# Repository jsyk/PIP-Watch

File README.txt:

----------------------------------------
Personal Information Panel - PIP Watch
----------------------------------------

Personal Information Panel – PIP Watch – is an open-source smart watch with an ePaper (EPD) display, a Bluetooth connection, and a Li-Ion accumulator.

This is a work in progress... For more information please visit:
http://www.jsykora.info/?page_id=328

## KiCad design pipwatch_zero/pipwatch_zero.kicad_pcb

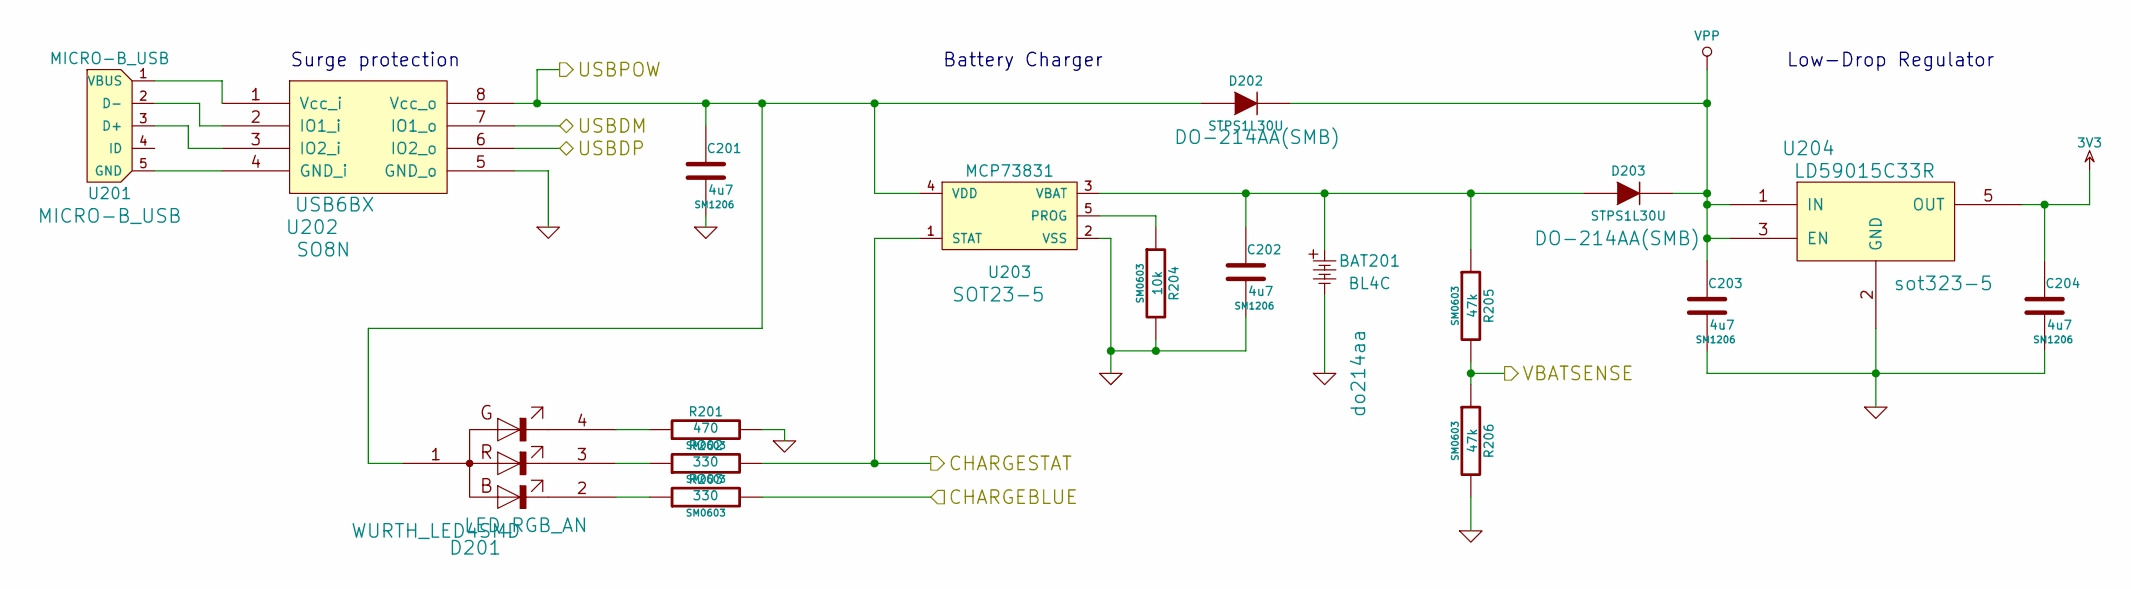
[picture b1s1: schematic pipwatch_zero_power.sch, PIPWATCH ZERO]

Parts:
BAT201: BL4C; do214aa
C201, C202, C203, C204: 4u7; SM1206
D201: LED_RGB_AN; WURTH_LED4SMD
D202, D203: STPS1L30U; DO-214AA(SMB)
R201: 470; SM0603
R202, R203: 330; SM0603
R204: 10k; SM0603
R205, R206: 47k; SM0603
U201: MICRO-B_USB
U202: USB6BX; SO8N
U203: MCP73831; SOT23-5
U204: LD59015C33R; sot323-5

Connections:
3V3: C204.1, U204.5 (OUT); also elsewhere on the board
/Battery and Power/CHARGEBLUE: R203.2; also elsewhere on the board
/Battery and Power/CHARGESTAT: R202.2, U203.1 (STAT); also elsewhere on the board
/Battery and Power/USBDM: U202.7 (IO1_o); also elsewhere on the board
/Battery and Power/USBDP: U202.6 (IO2_o); also elsewhere on the board
/Battery and Power/USBPOW: C201.1, D201.1, D202.1 (A), U202.8 (Vcc_o), U203.4 (VDD); also elsewhere on the board
/Battery and Power/VBATSENSE: R205.2, R206.1; also elsewhere on the board
GND: BAT201.2, C201.2, C202.2, C203.2, C204.2, R201.2, R204.2, R206.2, U202.5 (GND_o), U203.2 (VSS), U204.2 (GND); also elsewhere on the board
unnamed: R204.1, U203.5 (PROG)
unnamed: D201.4, R201.1
unnamed: D201.3, R202.1
unnamed: D201.2, R203.1
unnamed: U201.3 (D+), U202.3 (IO2_i)
unnamed: U201.2 (D-), U202.2 (IO1_i)
unnamed: U201.1 (VBUS), U202.1 (Vcc_i)
unnamed: U201.5 (GND), U202.4 (GND_i)
unnamed: BAT201.1, C202.1, D203.1 (A), R205.1, U203.3 (VBAT)
VPP: C203.1, D202.2 (K), D203.2 (K), U204.1 (IN), U204.3 (EN); also elsewhere on the board

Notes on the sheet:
Surge protection
Battery Charger
Low-Drop Regulator

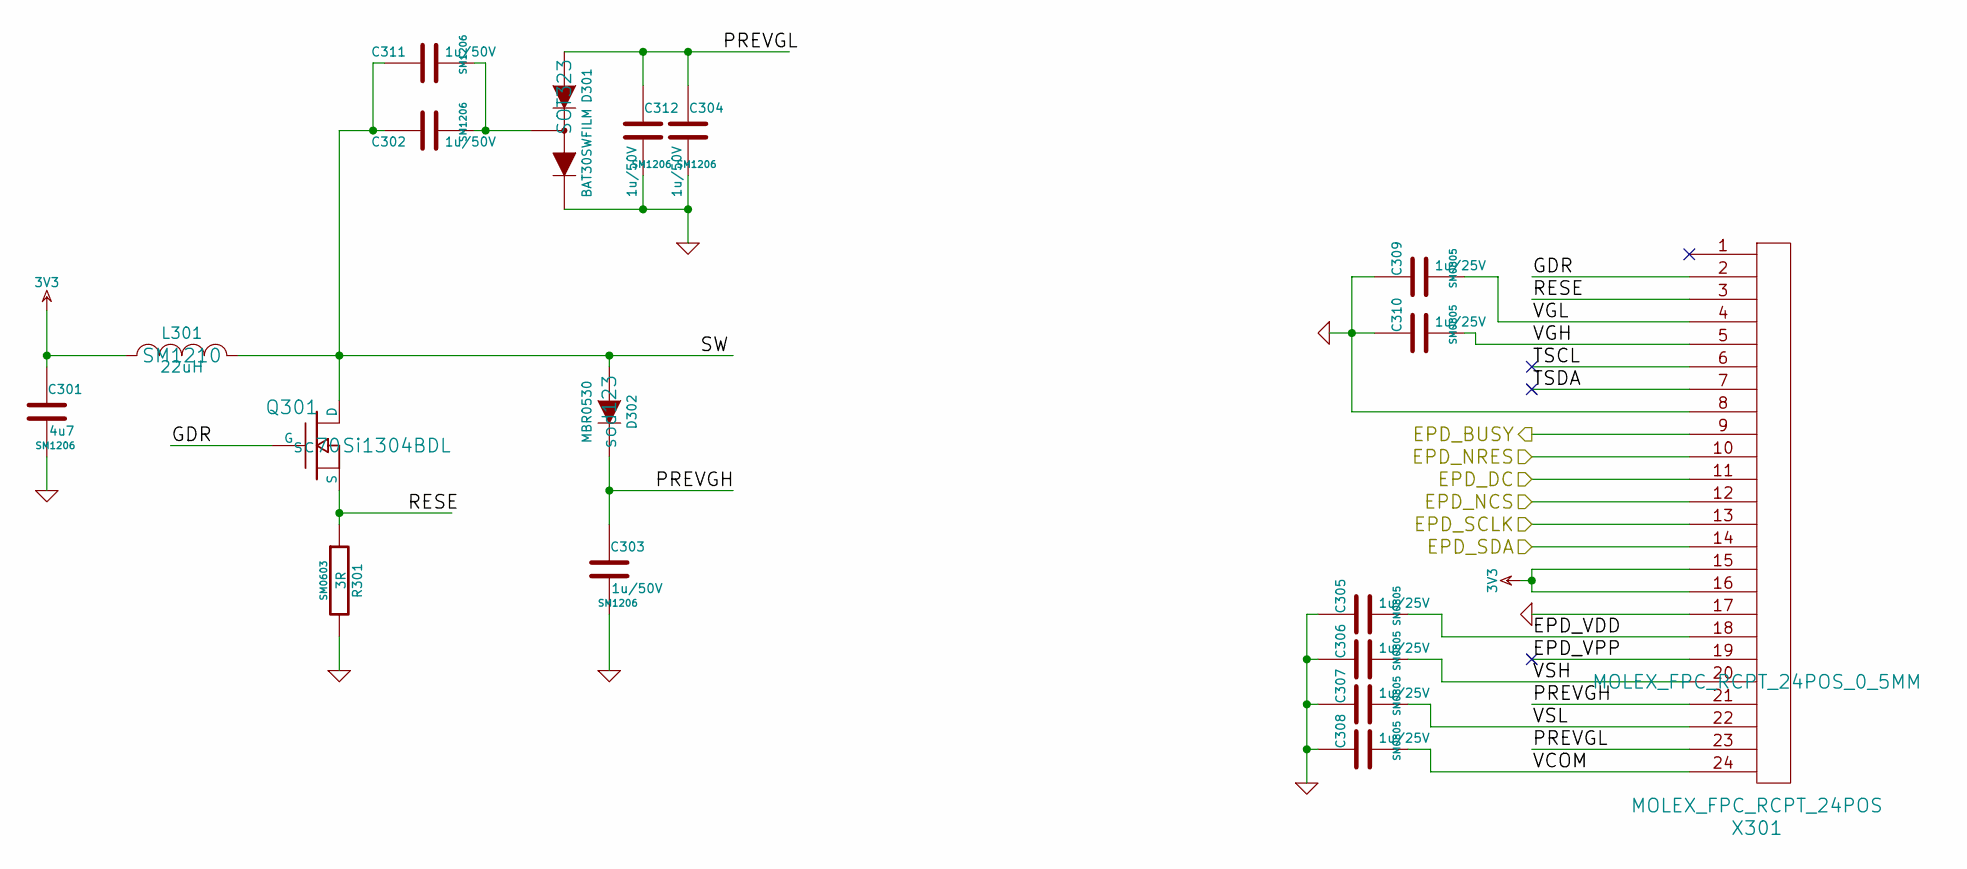
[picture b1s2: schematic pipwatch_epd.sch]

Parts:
C301: 4u7; SM1206
C302, C303, C304, C311, C312: 1u/50V; SM1206
C305, C306, C307, C308, C309, C310: 1u/25V; SM0805
D301: BAT30SWFILM; SOT323
D302: MBR0530; sod123
L301: 22uH; SM1210
Q301: Si1304BDL; sc70
R301: 3R; SM0603
X301: MOLEX_FPC_RCPT_24POS; MOLEX_FPC_RCPT_24POS_0_5MM

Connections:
3V3: C301.1, L301.1, X301.15, X301.16; also elsewhere on the board
/CPU/EPD_BUSY: X301.9; also elsewhere on the board
/CPU/EPD_DC: X301.11; also elsewhere on the board
/CPU/EPD_NCS: X301.12; also elsewhere on the board
/CPU/EPD_NRES: X301.10; also elsewhere on the board
/CPU/EPD_SCLK: X301.13; also elsewhere on the board
/CPU/EPD_SDA: X301.14; also elsewhere on the board
/EP-Display/EPD_VDD: C305.2, X301.18
/EP-Display/GDR: Q301.1 (G), X301.2
/EP-Display/PREVGH: C303.1, D302.2 (K), X301.21
/EP-Display/PREVGL: C304.1, C312.1, D301.1 (A), X301.23
/EP-Display/RESE: Q301.3 (S), R301.1, X301.3
/EP-Display/SW: C302.1, C311.1, D302.1 (A), L301.2, Q301.2 (D)
/EP-Display/VCOM: C308.2, X301.24
/EP-Display/VGH: C310.2, X301.5
/EP-Display/VGL: C309.2, X301.4
/EP-Display/VSH: C306.2, X301.20
/EP-Display/VSL: C307.2, X301.22
GND: C301.2, C303.2, C304.2, C305.1, C306.1, C307.1, C308.1, C309.1, C310.1, C312.2, D301.2 (K), R301.2, X301.8, X301.17; also elsewhere on the board
unnamed: C302.2, C311.2, D301.3 (Com)

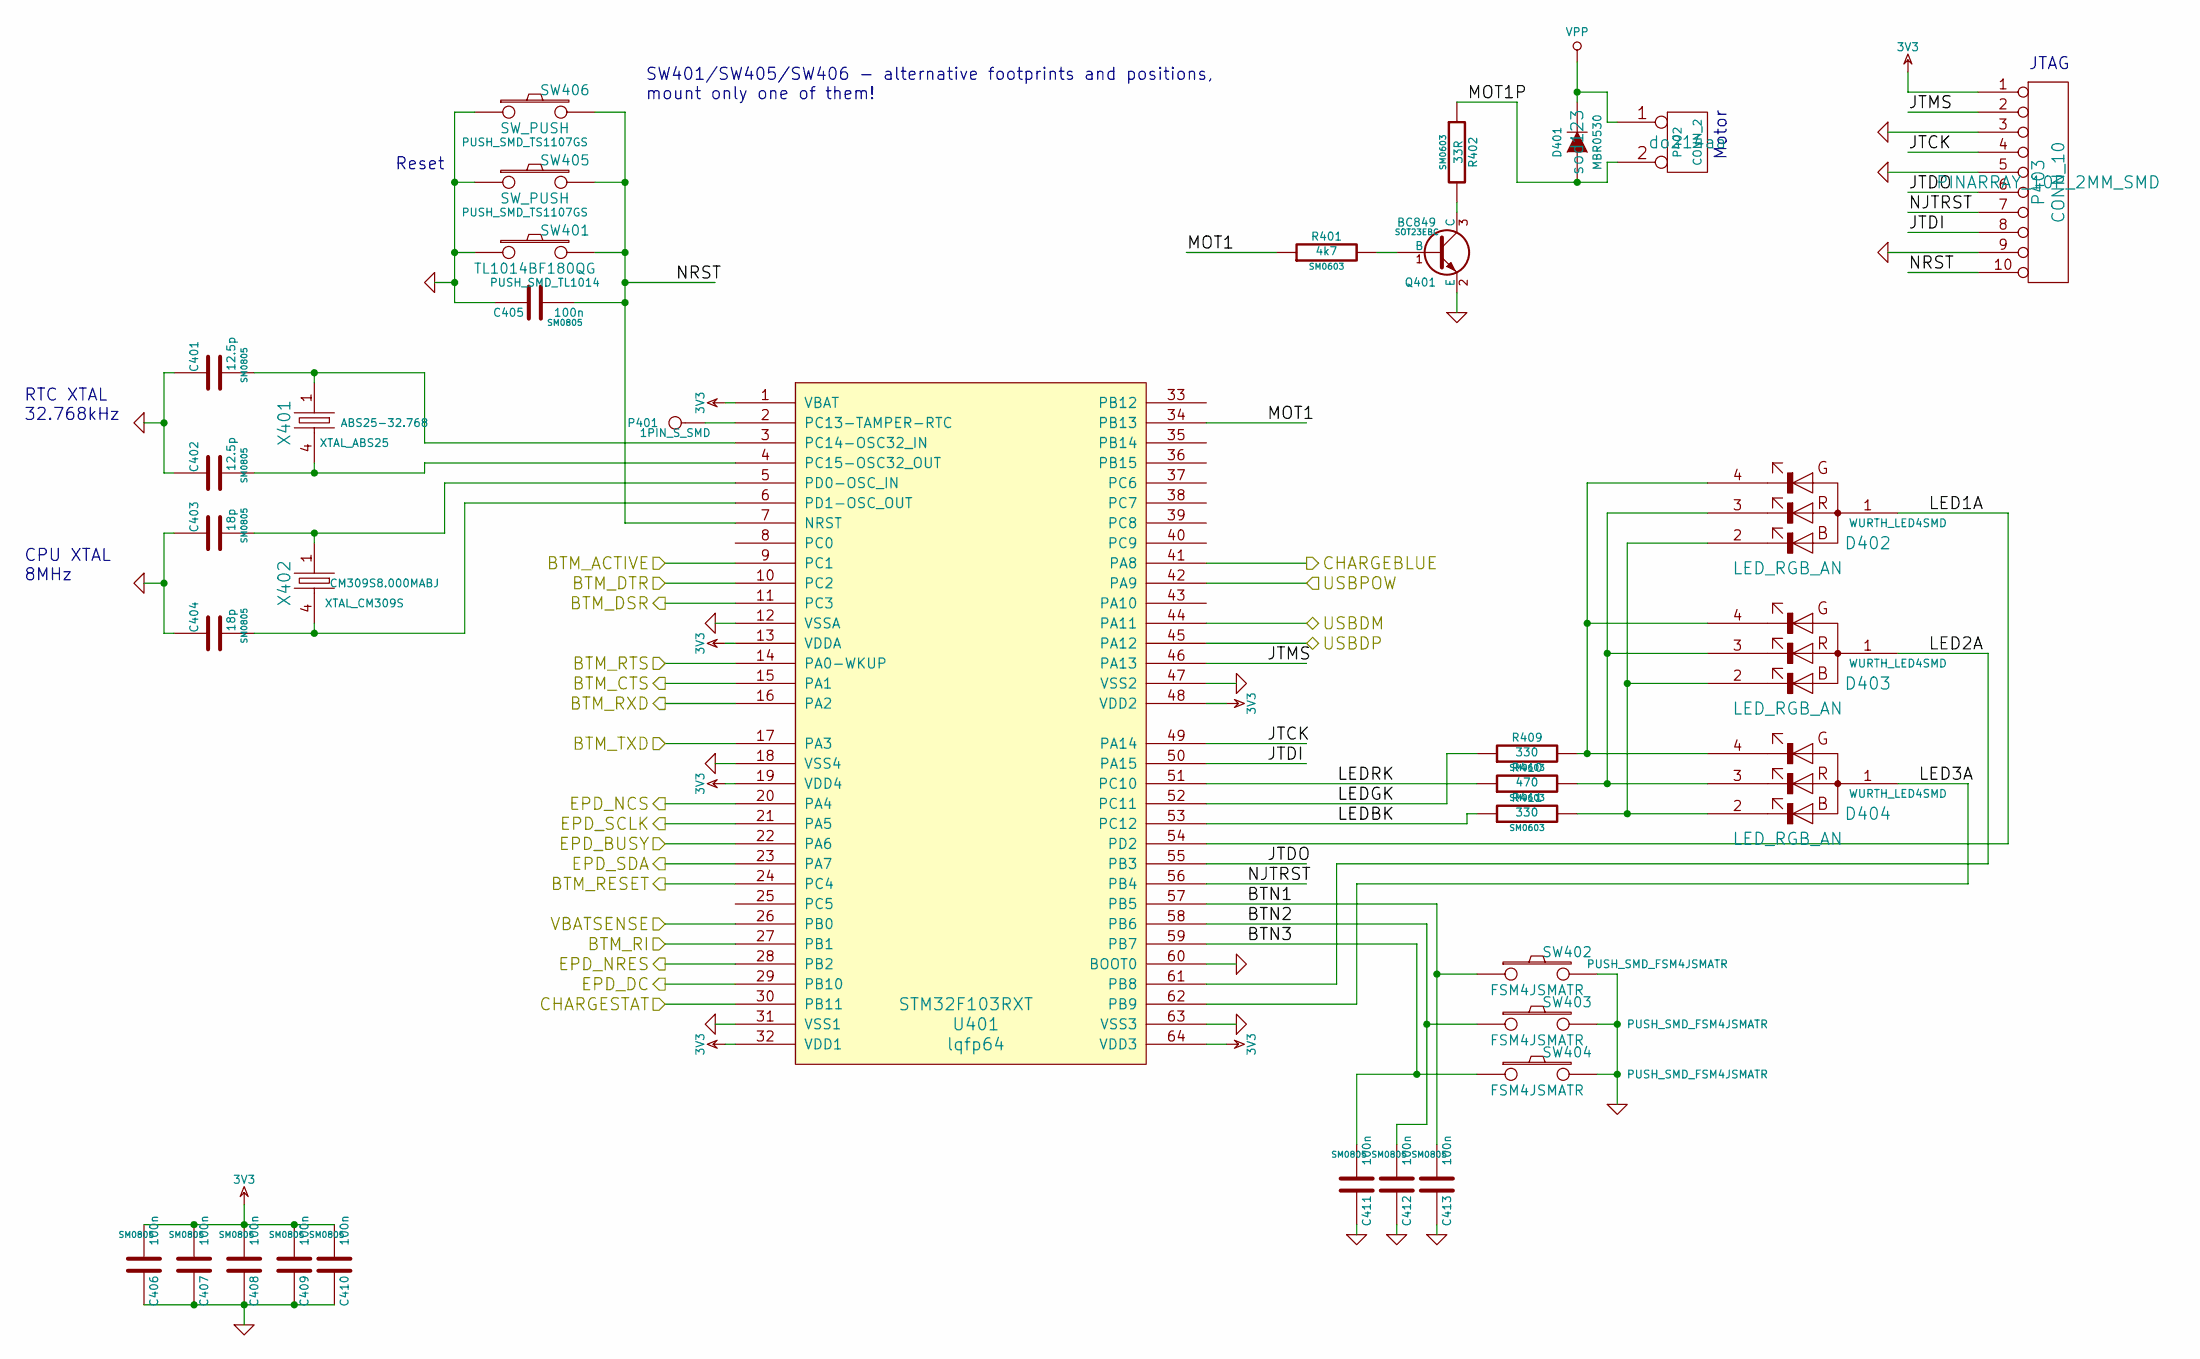
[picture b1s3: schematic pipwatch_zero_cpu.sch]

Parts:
C401, C402: 12.5p; SM0805
C403, C404: 18p; SM0805
C405, C406, C407, C408, C409, C410, C411, C412, C413: 100n; SM0805
D401: MBR0530; sod123
D402, D403, D404: LED_RGB_AN; WURTH_LED4SMD
P401: CONN_1; 1PIN_S_SMD
P402: CONN_2; do214aa
P403: CONN_10; PINARRAY_10P_2MM_SMD
Q401: BC849; SOT23EBC
R401: 4k7; SM0603
R402: 33R; SM0603
R409, R411: 330; SM0603
R410: 470; SM0603
SW401: TL1014BF180QG; PUSH_SMD_TL1014
SW402, SW403, SW404: FSM4JSMATR; PUSH_SMD_FSM4JSMATR
SW405, SW406: SW_PUSH; PUSH_SMD_TS1107GS
U401: STM32F103RXT; lqfp64
X401: ABS25-32.768; XTAL_ABS25
X402: CM309S8.000MABJ; XTAL_CM309S

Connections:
3V3: C406.2, C407.2, C408.2, C409.2, C410.2, P403.1, U401.1 (VBAT), U401.13 (VDDA), U401.19 (VDD4), U401.32 (VDD1), U401.48 (VDD2), U401.64 (VDD3); also elsewhere on the board
/BT Modem/BTM_ACTIVE: U401.9 (PC1); also elsewhere on the board
/BT Modem/BTM_CTS: U401.15 (PA1); also elsewhere on the board
/BT Modem/BTM_DSR: U401.11 (PC3); also elsewhere on the board
/BT Modem/BTM_DTR: U401.10 (PC2); also elsewhere on the board
/BT Modem/BTM_RESET: U401.24 (PC4); also elsewhere on the board
/BT Modem/BTM_RI: U401.27 (PB1); also elsewhere on the board
/BT Modem/BTM_RTS: U401.14 (PA0-WKUP); also elsewhere on the board
/BT Modem/BTM_RXD: U401.16 (PA2); also elsewhere on the board
/BT Modem/BTM_TXD: U401.17 (PA3); also elsewhere on the board
/Battery and Power/CHARGEBLUE: U401.41 (PA8); also elsewhere on the board
/Battery and Power/CHARGESTAT: U401.30 (PB11); also elsewhere on the board
/Battery and Power/USBDM: U401.44 (PA11); also elsewhere on the board
/Battery and Power/USBDP: U401.45 (PA12); also elsewhere on the board
/Battery and Power/USBPOW: U401.42 (PA9); also elsewhere on the board
/Battery and Power/VBATSENSE: U401.26 (PB0); also elsewhere on the board
/CPU/BTN1: C413.2, SW402.1, U401.57 (PB5)
/CPU/BTN2: C412.2, SW403.1, U401.58 (PB6)
/CPU/BTN3: C411.2, SW404.1, U401.59 (PB7)
/CPU/EPD_BUSY: U401.22 (PA6); also elsewhere on the board
/CPU/EPD_DC: U401.29 (PB10); also elsewhere on the board
/CPU/EPD_NCS: U401.20 (PA4); also elsewhere on the board
/CPU/EPD_NRES: U401.28 (PB2); also elsewhere on the board
/CPU/EPD_SCLK: U401.21 (PA5); also elsewhere on the board
/CPU/EPD_SDA: U401.23 (PA7); also elsewhere on the board
/CPU/JTCK: P403.4, U401.49 (PA14)
/CPU/JTDI: P403.8, U401.50 (PA15)
/CPU/JTDO: P403.6, U401.55 (PB3)
/CPU/JTMS: P403.2, U401.46 (PA13)
/CPU/LED1A: D402.1, U401.54 (PD2)
/CPU/LED2A: D403.1, U401.61 (PB8)
/CPU/LED3A: D404.1, U401.62 (PB9)
/CPU/LEDBK: R411.1, U401.53 (PC12)
/CPU/LEDGK: R409.1, U401.52 (PC11)
/CPU/LEDRK: R410.1, U401.51 (PC10)
/CPU/MOT1: R401.1, U401.34 (PB13)
/CPU/MOT1P: D401.1 (A), P402.2 (PM), R402.1
/CPU/NJTRST: P403.7, U401.56 (PB4)
/CPU/NRST: C405.2, P403.10, SW401.2, SW405.2, SW406.2, U401.7 (NRST)
GND: C401.1, C402.1, C403.1, C404.1, C405.1, C406.1, C407.1, C408.1, C409.1, C410.1, C411.1, C412.1, C413.1, P403.3, P403.5, P403.9, Q401.2 (E), SW401.1, SW402.2, SW403.2, SW404.2, SW405.1, SW406.1, U401.12 (VSSA), U401.18 (VSS4), U401.31 (VSS1), U401.47 (VSS2), U401.60 (BOOT0), U401.63 (VSS3); also elsewhere on the board
unnamed: C401.2, U401.3 (PC14-OSC32_IN), X401.1
unnamed: C402.2, U401.4 (PC15-OSC32_OUT), X401.4
unnamed: Q401.1 (B), R401.2
unnamed: P401.1, U401.2 (PC13-TAMPER-RTC)
unnamed: D402.2, D403.2, D404.2, R411.2
unnamed: D402.3, D403.3, D404.3, R410.2
unnamed: D402.4, D403.4, D404.4, R409.2
unnamed: Q401.3 (C), R402.2
unnamed: C403.2, U401.5 (PD0-OSC_IN), X402.1
unnamed: C404.2, U401.6 (PD1-OSC_OUT), X402.4
VPP: D401.2 (K), P402.1; also elsewhere on the board

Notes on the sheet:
Reset
Motor
JTAG
SW401/SW405/SW406 - alternative footprints and positions, mount only one of them!
RTC XTAL 32.768kHz
CPU XTAL 8MHz

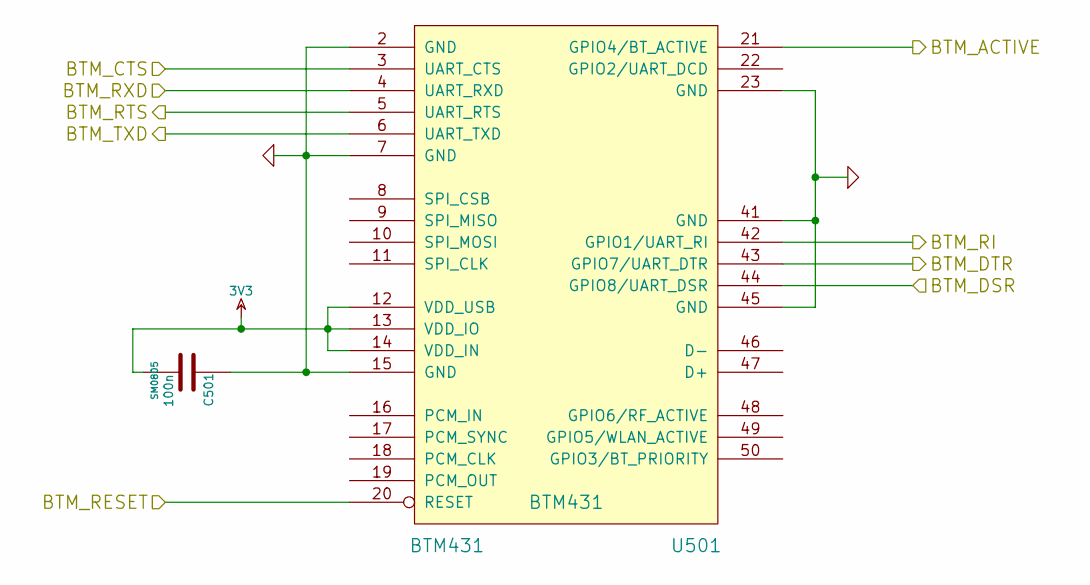
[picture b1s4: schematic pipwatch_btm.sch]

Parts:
C501: 100n; SM0805
U501: BTM431

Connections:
3V3: C501.2, U501.12 (VDD_USB), U501.13 (VDD_IO), U501.14 (VDD_IN); also elsewhere on the board
/BT Modem/BTM_ACTIVE: U501.21 (GPIO4/BT_ACTIVE); also elsewhere on the board
/BT Modem/BTM_CTS: U501.3 (UART_CTS); also elsewhere on the board
/BT Modem/BTM_DSR: U501.44 (GPIO8/UART_DSR); also elsewhere on the board
/BT Modem/BTM_DTR: U501.43 (GPIO7/UART_DTR); also elsewhere on the board
/BT Modem/BTM_RESET: U501.20 (RESET); also elsewhere on the board
/BT Modem/BTM_RI: U501.42 (GPIO1/UART_RI); also elsewhere on the board
/BT Modem/BTM_RTS: U501.5 (UART_RTS); also elsewhere on the board
/BT Modem/BTM_RXD: U501.4 (UART_RXD); also elsewhere on the board
/BT Modem/BTM_TXD: U501.6 (UART_TXD); also elsewhere on the board
GND: C501.1, U501.2 (GND), U501.7 (GND), U501.15 (GND), U501.23 (GND), U501.41 (GND), U501.45 (GND); also elsewhere on the board

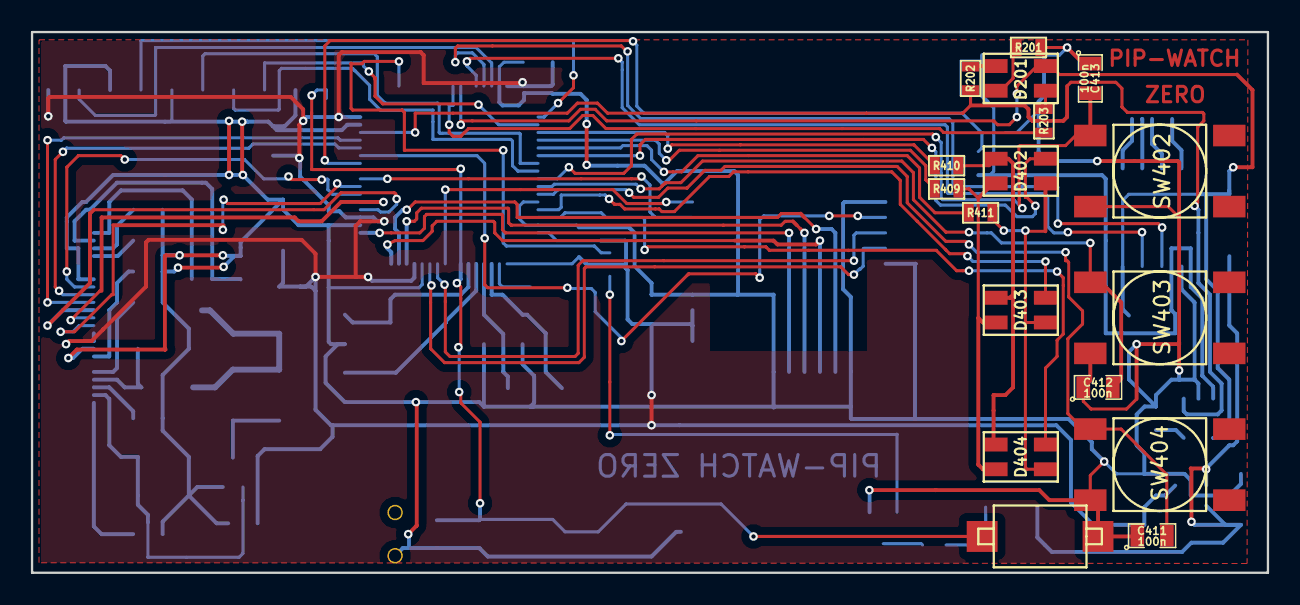
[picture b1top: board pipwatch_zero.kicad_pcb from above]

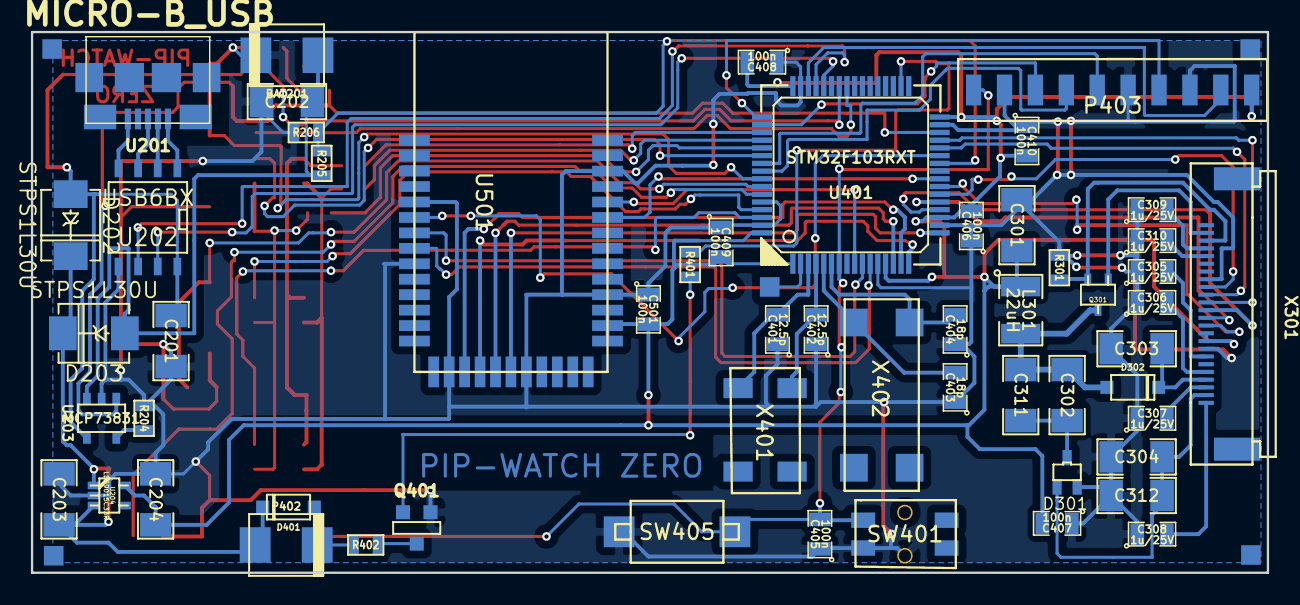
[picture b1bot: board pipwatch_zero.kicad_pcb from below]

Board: 2 copper layers, 80.0 x 35.0 mm, 77 parts (60 on the bottom side), 72 nets.

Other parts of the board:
1PIN_S_SMD, 1PIN_S_SMD#2, 1PIN_S_SMD#3, 1PIN_S_SMD#4: P***; 1PIN_S_SMD

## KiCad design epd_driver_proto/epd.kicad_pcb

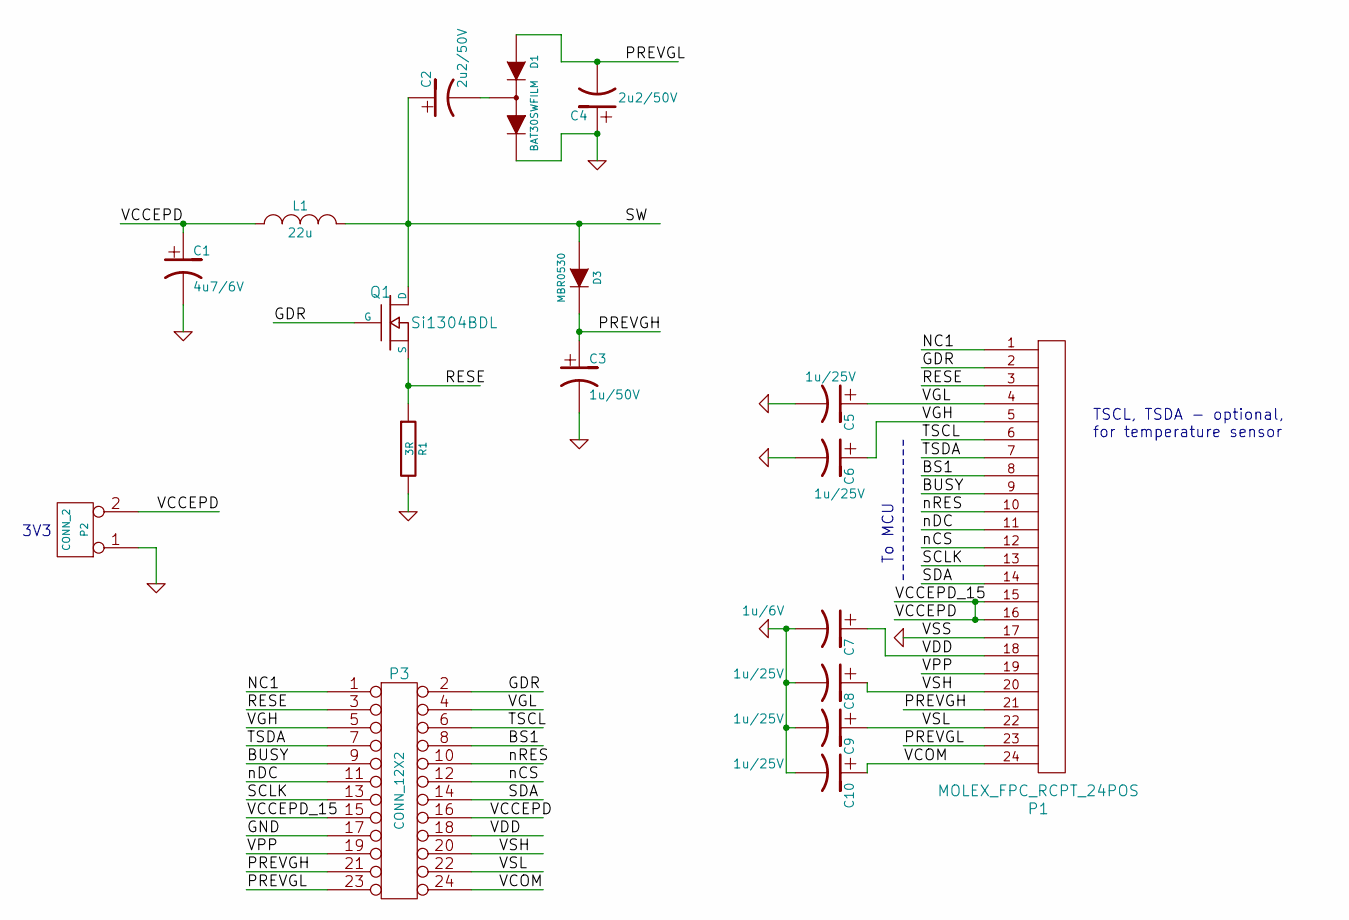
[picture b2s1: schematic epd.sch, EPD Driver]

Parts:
C1: 4u7/6V
C2, C4: 2u2/50V
C3: 1u/50V
C5, C6, C8, C9, C10: 1u/25V
C7: 1u/6V
D1: BAT30SWFILM
D3: MBR0530
L1: 22u
P1: MOLEX_FPC_RCPT_24POS
P2: CONN_2
P3: CONN_12X2
Q1: Si1304BDL
R1: 3R

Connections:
/BS1: P1.8, P3.8
/BUSY: P1.9, P3.9
/GDR: P1.2, P3.2, Q1.1 (G)
/NC1: P1.1, P3.1
/PREVGH: C3.1, D3.2 (K), P1.21, P3.21
/PREVGL: C4.2, D1.1 (A), P1.23, P3.23
/RESE: P1.3, P3.3, Q1.3 (S), R1.1
/SCLK: P1.13, P3.13
/SDA: P1.14, P3.14
/SW: C2.1, D3.1 (A), L1.2, Q1.2 (D)
/TSCL: P1.6, P3.6
/TSDA: P1.7, P3.7
/VCCEPD: C1.1, L1.1, P1.15, P1.16, P2.2 (PM), P3.15, P3.16
/VCOM: C10.1, P1.24, P3.24
/VDD: C7.1, P1.18, P3.18
/VGH: C6.1, P1.5, P3.5
/VGL: C5.1, P1.4, P3.4
/VPP: P1.19, P3.19
/VSH: C8.1, P1.20, P3.20
/VSL: C9.1, P1.22, P3.22
/nCS: P1.12, P3.12
/nDC: P1.11, P3.11
/nRES: P1.10, P3.10
GND: C1.2, C3.2, C4.1, C5.2, C6.2, C7.2, C8.2, C9.2, C10.2, D1.2 (K), P1.17, P2.1, P3.17, R1.2
unnamed: C2.2, D1.3 (Com)

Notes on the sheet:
TSCL, TSDA - optional, for temperature sensor
To MCU
3V3

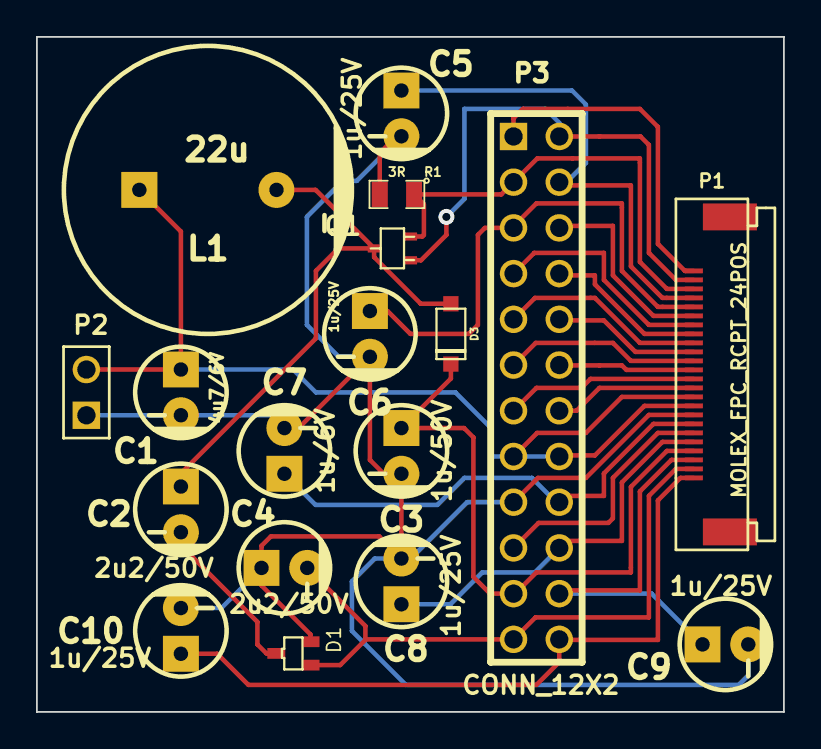
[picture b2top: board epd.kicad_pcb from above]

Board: 2 copper layers, 41.5 x 37.5 mm, 18 parts (0 on the bottom side), 25 nets.

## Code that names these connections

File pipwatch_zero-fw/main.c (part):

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
    /* ------------------------------------------------------------------------ */
    /* Buttons */
    /* Configure GPIO pins : PB5,6,7 = Buttons 0, 1, 2 */
    GPIO_InitStruct.GPIO_Pin = GPIO_Pin_5 | GPIO_Pin_6 | GPIO_Pin_7;
    GPIO_InitStruct.GPIO_Mode = GPIO_Mode_IPU;
    GPIO_InitStruct.GPIO_Speed = GPIO_Speed_2MHz;
    GPIO_Init(GPIOB, &GPIO_InitStruct);

    /* USBPOW (PA9) input pull-down */
    GPIO_InitStruct.GPIO_Pin = USBPOW_Pin;
    GPIO_InitStruct.GPIO_Mode = GPIO_Mode_IPD;
    GPIO_InitStruct.GPIO_Speed = GPIO_Speed_2MHz;
    GPIO_Init(USBPOW_Port, &GPIO_InitStruct);

    /* CHARGESTAT (PB11) input pull-up */
    GPIO_InitStruct.GPIO_Pin = GPIO_Pin_11;
    GPIO_InitStruct.GPIO_Mode = GPIO_Mode_IPU;
    GPIO_InitStruct.GPIO_Speed = GPIO_Speed_2MHz;
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
    /* set EXTI sources */
    GPIO_EXTILineConfig(GPIO_PortSourceGPIOB, GPIO_PinSource5); // BTN0
    GPIO_EXTILineConfig(GPIO_PortSourceGPIOB, GPIO_PinSource6); // BTN1
    GPIO_EXTILineConfig(GPIO_PortSourceGPIOB, GPIO_PinSource7); // BTN2
    // GPIO_EXTILineConfig(GPIO_PortSourceGPIOA, GPIO_PinSource9); // USBPOW

#if 1
    /* all the interrupts go to the EXTI9_5_IRQn IRQ-line */
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    
    /* ------------------------------------------------------------------------ */
    /* LEDs */
    /* Configure GPIO pin : PC10=LEDRK, PC11=LEDGK, PC12=LEDBK Output */
    GPIO_InitStruct.GPIO_Pin = GPIO_Pin_10 | GPIO_Pin_11 | GPIO_Pin_12;
    GPIO_InitStruct.GPIO_Mode = GPIO_Mode_Out_PP;
    GPIO_InitStruct.GPIO_Speed = GPIO_Speed_2MHz;
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    /* set cathodes HI */
    GPIO_SetBits(GPIOC, GPIO_Pin_10 | GPIO_Pin_11 | GPIO_Pin_12);

    /* Configure GPIO pin : PD2=LED1A,  Output */
    GPIO_InitStruct.GPIO_Pin = GPIO_Pin_2;
    GPIO_InitStruct.GPIO_Mode = GPIO_Mode_Out_PP;
    GPIO_InitStruct.GPIO_Speed = GPIO_Speed_2MHz;
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    /* set anode LO */
    GPIO_ResetBits(GPIOD, GPIO_Pin_2);

    /* Configure GPIO pin : PB8=LED2A, PB9=LED3A, Output */
    GPIO_InitStruct.GPIO_Pin = GPIO_Pin_8 | GPIO_Pin_9;
    GPIO_InitStruct.GPIO_Mode = GPIO_Mode_Out_PP;
    GPIO_InitStruct.GPIO_Speed = GPIO_Speed_2MHz;
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    /* set anode LO */
    GPIO_ResetBits(GPIOB, GPIO_Pin_8 | GPIO_Pin_9);

    /* The CHARGEBLUE LED (PA8): Set high-impedence floating -> no current  */
    GPIO_InitStruct.GPIO_Pin = GPIO_Pin_8;
    GPIO_InitStruct.GPIO_Mode = GPIO_Mode_IN_FLOATING;
    GPIO_InitStruct.GPIO_Speed = GPIO_Speed_2MHz;
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
    /* ------------------------------------------------------------------------ */
    /* Motors */
    /* Configure GPIO pin : PB13 Output */
    GPIO_InitStruct.GPIO_Pin = MOTOR_Pin;
    GPIO_InitStruct.GPIO_Mode = GPIO_Mode_Out_PP;
    GPIO_InitStruct.GPIO_Speed = GPIO_Speed_2MHz;
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    /* ------------------------------------------------------------------------ */
    /* BTM GPIO Signals */
#if 0
    /* Configure GPIO pin : PC4=BTM_RESET,  Output */
    GPIO_InitStruct.GPIO_Pin = BTM_Reset_Pin;
    GPIO_InitStruct.GPIO_Mode = GPIO_Mode_Out_PP;
    GPIO_InitStruct.GPIO_Speed = GPIO_Speed_10MHz;
    GPIO_Init(BTM_Reset_Port, &GPIO_InitStruct);
    GPIO_SetBits(BTM_Reset_Port, BTM_Reset_Pin);
#endif

    /* ------------------------------------------------------------------------ */
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
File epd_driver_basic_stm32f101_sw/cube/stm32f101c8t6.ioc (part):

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Mcu.Name=STM32F101C(8-B)Tx
Mcu.Package=LQFP48
Mcu.UserName=STM32F101C8Tx
PA1.GPIOParameters=GPIO_Speed,GPIO_Mode
PA1.GPIO_Mode=GPIO_Mode_Out_PP
PA1.GPIO_Speed=GPIO_Speed_50MHz
PA1.Signal=GPIO_Output
PA10.GPIOParameters=GPIO_Speed,GPIO_Mode
PA10.GPIO_Mode=GPIO_Mode_AF_PP
PA10.GPIO_Speed=GPIO_Speed_2MHz
PA10.Mode=Hardware-flow-control
PA10.Signal=USART1_RX
PA11.GPIOParameters=GPIO_Speed,GPIO_Mode
PA11.GPIO_Mode=GPIO_Mode_AF_PP
PA11.GPIO_Speed=GPIO_Speed_2MHz
PA11.Mode=Hardware-flow-control
PA11.Signal=USART1_CTS
PA12.GPIOParameters=GPIO_Speed,GPIO_Mode
PA12.GPIO_Mode=GPIO_Mode_AF_PP
PA12.GPIO_Speed=GPIO_Speed_2MHz
PA12.Mode=Hardware-flow-control
PA12.Signal=USART1_RTS
PA13.Mode=JTAG(5-pin)
PA13.Signal=SYS_JTMS-SWDIO
PA14.Mode=JTAG(5-pin)
PA14.Signal=SYS_JTCK-SWCLK
PA15.Mode=JTAG(5-pin)
PA15.Signal=SYS_JTDI
PA2.GPIOParameters=GPIO_Speed,GPIO_Mode
PA2.GPIO_Mode=GPIO_Mode_Out_PP
PA2.GPIO_Speed=GPIO_Speed_50MHz
PA2.Signal=GPIO_Output
PA3.GPIOParameters=GPIO_Speed,GPIO_Mode
PA3.GPIO_Mode=GPIO_Mode_Out_PP
PA3.GPIO_Speed=GPIO_Speed_50MHz
PA3.Signal=GPIO_Output
PA4.GPIOParameters=GPIO_Speed,GPIO_Mode
PA4.GPIO_Mode=GPIO_Mode_Out_PP
PA4.GPIO_Speed=GPIO_Speed_50MHz
PA4.Signal=GPIO_Output
PA5.GPIOParameters=GPIO_Speed,GPIO_Mode
PA5.GPIO_Mode=GPIO_Mode_AF_PP
PA5.GPIO_Speed=GPIO_Speed_50MHz
PA5.Mode=TX-Only-Simplex-Unidirect-Master
PA5.Signal=SPI1_SCK
PA6.GPIOParameters=GPIO_Mode
PA6.GPIO_Mode=GPIO_Mode_IPU
PA6.Signal=GPIO_Input
PA7.GPIOParameters=GPIO_Speed,GPIO_Mode
PA7.GPIO_Mode=GPIO_Mode_AF_PP
PA7.GPIO_Speed=GPIO_Speed_50MHz
PA7.Mode=TX-Only-Simplex-Unidirect-Master
PA7.Signal=SPI1_MOSI
PA9.GPIOParameters=GPIO_Speed,GPIO_Mode
PA9.GPIO_Mode=GPIO_Mode_AF_PP
PA9.GPIO_Speed=GPIO_Speed_2MHz
PA9.Mode=Hardware-flow-control
PA9.Signal=USART1_TX
PB3.Mode=JTAG(5-pin)
PB3.Signal=SYS_JTDO-TRACESWO
PB4.Mode=JTAG(5-pin)
PB4.Signal=SYS_JTRST

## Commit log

2014-05-17 EPD Driver prototype board with MOLEX FPC, pin header, and mosfet
2014-05-17 documentation directory
2014-05-17 documentation, license
2014-05-17 move third-party docs to special directory
2014-05-17 add README.txt / incomplete
2014-05-17 README: link to my website
2014-05-19 global bom; a picture of aspects
2014-06-18 epd_driver_basic_stm32f101_sw: basic STM software for driving epd_driver_proto hardware
2014-06-18 updated BOM, added pdf of the battery charger MCP73831T
2014-06-29 add comments
2014-06-29 FreeRTOS v8.0.1 source
2014-06-29 u8glib source, with a small modification in u8g_pb8v2.c
2014-06-29 SSD1606 datasheet - the MCU integrated in the EPD display
2014-06-29 update gitignore
2014-06-29 stm32f103_rtos_u8glib_epd: epd_driver_proto(hw) + STM32F103 + FreeRTOS + u8g = draws simple text
2014-06-29 move ST_Library directory to top level
2014-06-29 some missing documentation files
2014-06-30 u8g_pbxv2.c: vertical bytes, 2b deep, page height
2014-07-02 doc/ pictures for web
2014-07-22 fix usart2: rcc, basic bluetooth modem
2014-07-22 u8g_epd_btm: Prints text received over BT modem on EPD. Basic RTC config.
2014-07-23 power saving: WFI in Idle, slow clock. Clock face drawing
2014-07-26 stm32f103_rtos_u8g_epd_btm: rtclock, reorganize files
2014-07-26 battery voltage measurement
2014-07-27 utils
2014-07-29 update global BOM
2014-07-29 doc/swarch.svg, swtasks.svg
2014-07-29 pipwatch_zero: started hardware schema
2014-08-13 hw drawing (started), sw fixes for presentation
2014-08-23 pipwatch_zero: basic schema complete
2014-08-24 pipwatch_zero: footprints
2014-08-31 pipwarch-zero: started layout
2014-08-31 doc/third-party pdf files
2014-08-31 pipwatch_zero layout complete
2014-09-03 pipwatch_zero hw02, sent to pragoboard
2014-09-03 doc/third-party
2014-09-07 hw02 schematic pdf
2014-09-14 sw pipwatch_zero_rtos_u8g_epd_btm; somewhat working, bugs in hw
2014-09-18 auto-off LEDs after a timeout
2014-09-18 leds comments
2014-09-20 new bluetooth works; buttons via irq still dont
2014-09-21 buttons work
2014-09-22 bt-modem work, motor
2014-09-26 btm.c: low-power optimization: page-scan interval 1.25s
2014-09-28 comments
2014-10-01 do not print CONNECT, RING and NO CARRIER to the display
2014-10-05 rename dirs; protocol work
2014-10-07 btm.c decoding
2014-10-13 gui work, integreate jsmn (JSON decoder)
2014-10-14 use new btm session link parser
2014-10-21 btm parser work
2014-10-22 fixed jtag low-power issue; app-link work
2014-10-23 epd experiments; basic sms print
2014-10-25 new guitextbox
2014-10-25 move textlines to utils
2014-10-25 initial menu (stub)
2014-10-26 update range experiments
2014-12-09 many changes
2014-12-13 ignore .dropbox.attr files
2014-12-13 add LUT data from STM3232323232323232323232323232323232323232323232323232323232323232Cube0L
